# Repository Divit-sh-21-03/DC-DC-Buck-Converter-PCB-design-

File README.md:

# LMR51450 DC-DC Buck Converter

This repository contains the complete KiCad design files for a DC-DC buck (step-down) converter using the Texas Instruments LMR51450 synchronous buck regulator. The design has been optimized for stable performance and low electrical noise (EMI).

## Key Specifications

* **Integrated Circuit:** Texas Instruments LMR51450
* **Input Voltage:** 10V - 35V DC
* **Output Voltage:** 7.6V DC
* **Maximum Output Current:** 4A
* **Switching Frequency:** Approximately 460 kHz

## Repository Contents

* **KiCad Project Files**: The project contains `.kicad_sch` (schematic), and `.kicad_pcb` (PCB layout) and `BOM` files.
* **Media**: This folder contains screenshots of the final schematic and PCB layout.

## Design Notes

The PCB layout was carefully designed to minimize EMI and ensure stable operation under high load. Key considerations include:
* Minimization of critical high-frequency current loop areas.
* Use of solid top and bottom ground planes for low-impedance current return paths.
* Strategic placement of input and output capacitors to reduce voltage ripple.

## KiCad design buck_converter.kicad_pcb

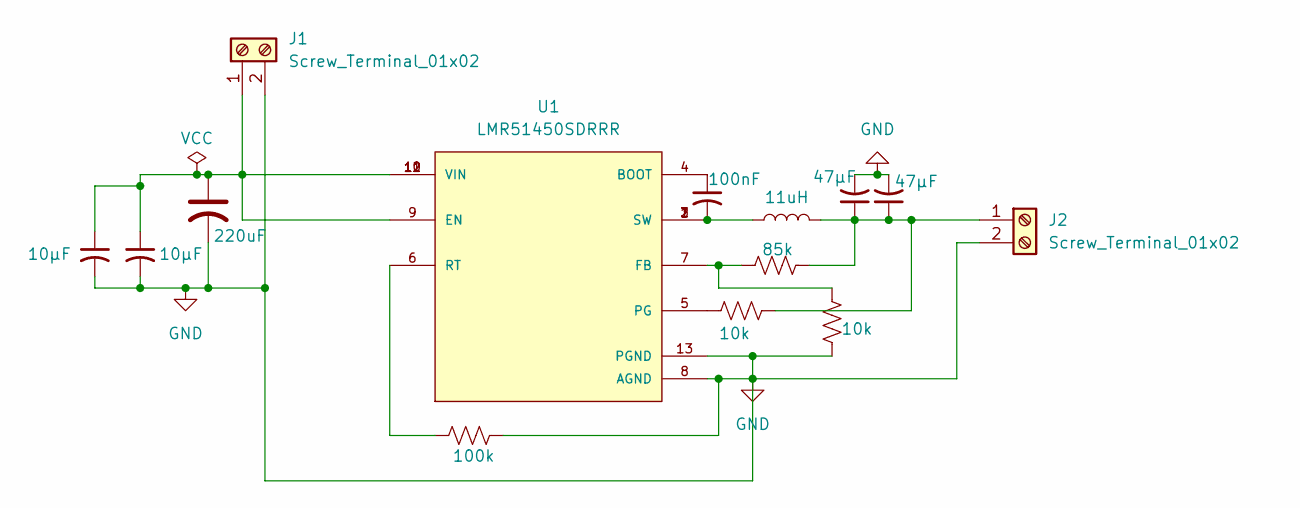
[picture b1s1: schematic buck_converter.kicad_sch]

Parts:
C1: 220uF; C_Disc_D3.0mm_W1.6mm_P2.50mm
C2: 100nF; C_Disc_D3.0mm_W1.6mm_P2.50mm
C3, C4: 47µF; C_Disc_D3.0mm_W1.6mm_P2.50mm
C5, C6: 10µF; C_Disc_D3.0mm_W1.6mm_P2.50mm
J1, J2: Screw_Terminal_01x02; TerminalBlock_Altech_AK300-2_P5.00mm
L1: 11uH; L_Radial_D6.0mm_P4.00mm
R1: 85k; R_Axial_DIN0204_L3.6mm_D1.6mm_P1.90mm_Vertical
R2, R4: 10k; R_Axial_DIN0204_L3.6mm_D1.6mm_P1.90mm_Vertical
R3: 100k; R_Axial_DIN0204_L3.6mm_D1.6mm_P1.90mm_Vertical
U1: LMR51450SDRRR; CONV_LMR51450SDRRR; PARTREV December 2022

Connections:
GND: C1.2, C3.2, C4.2, C5.2, C6.2, J1.2, J2.2, R2.1, R3.1, U1.8 (AGND), U1.13 (PGND)
unnamed: C2.2, L1.1, U1.1 (SW), U1.2 (SW), U1.3 (SW)
unnamed: C1.1, C5.1, C6.1, J1.1, U1.9 (EN), U1.10 (VIN), U1.11 (VIN), U1.12 (VIN)
unnamed: C3.1, C4.1, J2.1, L1.2, R1.1, R4.1
unnamed: C2.1, U1.4 (BOOT)
unnamed: R1.2, R2.2, U1.7 (FB)
unnamed: R4.2, U1.5 (PG)
unnamed: R3.2, U1.6 (RT)

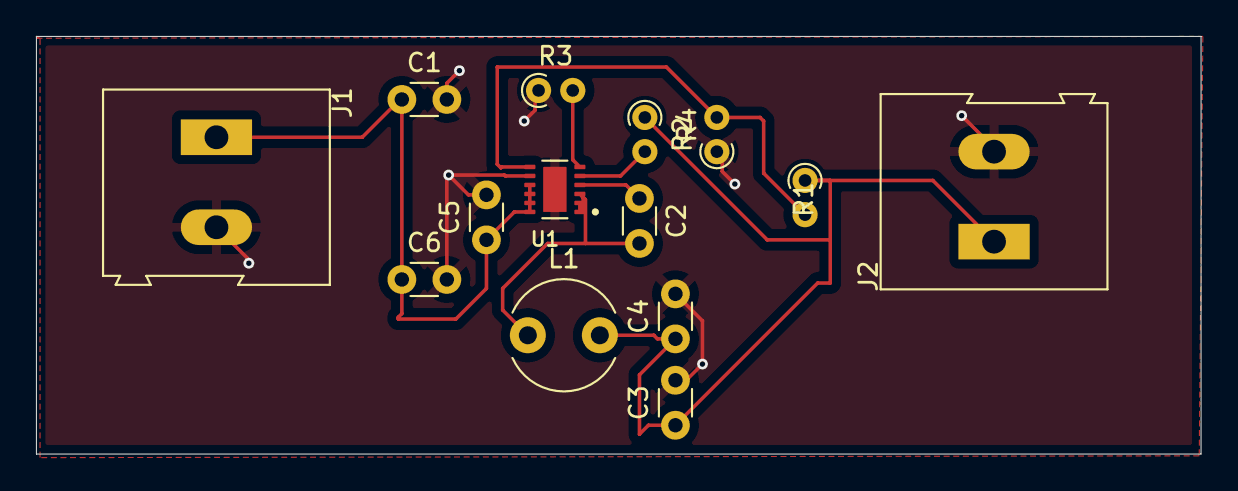
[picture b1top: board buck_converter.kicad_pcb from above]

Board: 2 copper layers, 64.7 x 23.2 mm, 14 parts (0 on the bottom side), 8 nets.

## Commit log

2025-09-14 Create media
2025-09-14 Rename Screenshot 2025-09-14 122508.png to PCB_bothlayer.png
2025-09-14 Rename Screenshot 2025-09-14 122622.png to sch.png
